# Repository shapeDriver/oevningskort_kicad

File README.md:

# oevningskort_kicad
Repeterar skolkunskap genom ett enkelt mönsterkortsprojekt som sammankopplar en Arduino Nano v3.x med enklare genomhålskomponenter.

Tungt baserad på HTM Workshops KiCad handledningsvideoserie: https://www.youtube.com/playlist?list=PLUOaI24LpvQPls1Ru_qECJrENwzD7XImd

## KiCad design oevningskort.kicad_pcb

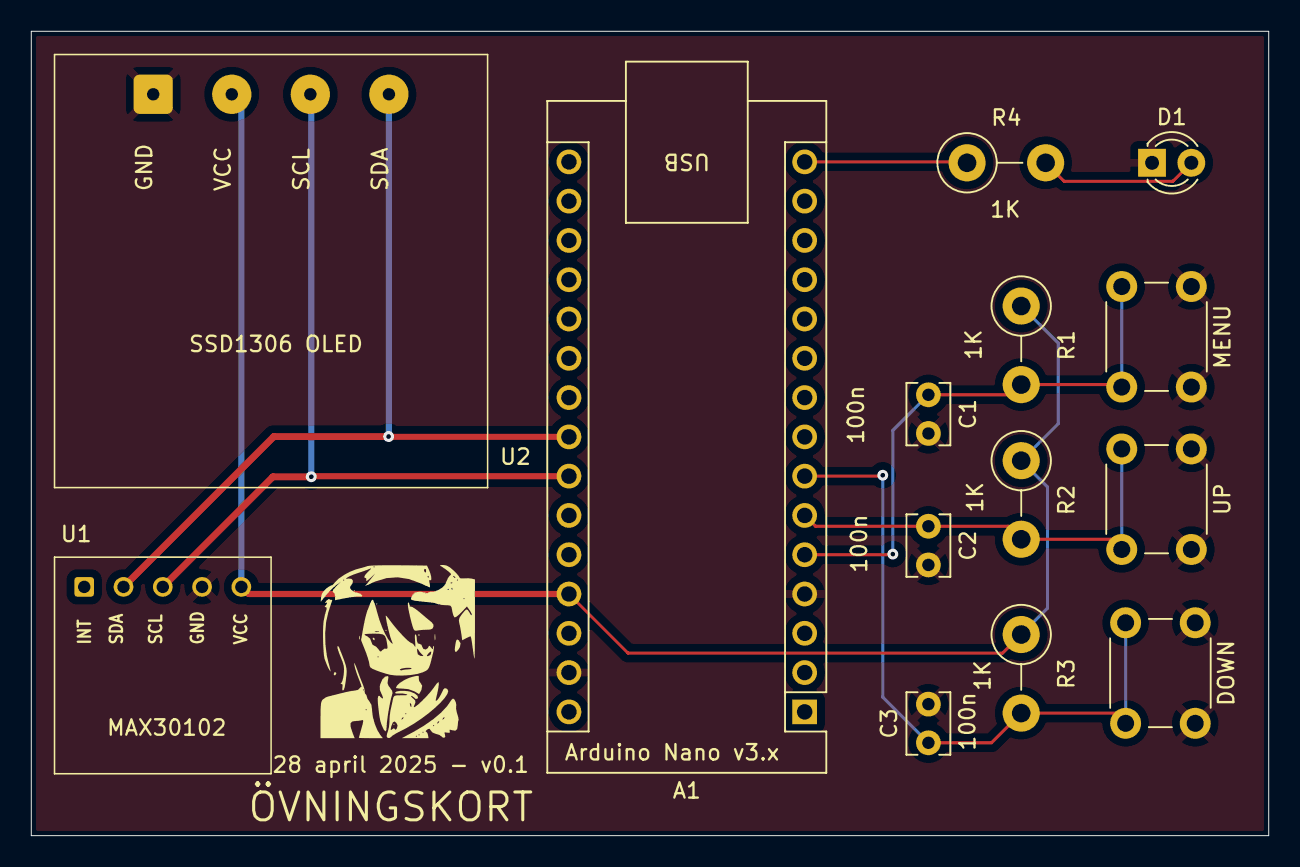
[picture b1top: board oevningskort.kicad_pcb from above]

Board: 2 copper layers, 80.0 x 52.0 mm, 14 parts (0 on the bottom side), 9 nets.

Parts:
A1: Arduino_Nano_v3.x; Arduino_Nano
C1, C2, C3: 100n; C_Disc_D3.8mm_W2.6mm_P2.50mm
D1: ALARM; LED_D3.0mm
DOWN: SW_Push; SW_PUSH_6mm
MENU: SW_Push; SW_PUSH_6mm
R1, R2, R3, R4: 1K; R_Axial_DIN0411_L9.9mm_D3.6mm_P5.08mm_Vertical
U1: MAX30102; MAX30102_module
U2: SSD1306
UP: SW_Push; SW_PUSH_6mm

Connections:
+5V: A1.27 (+5V), R1.1, R2.1, R3.1, U1.5 (VCC), U2.2 (VCC)
GND: A1.4 (GND), A1.29 (GND), C1.2, C2.2, C3.2, D1.1 (K), DOWN.1, MENU.1, U1.4 (GND), U2.1 (GND), UP.1
unnamed: A1.23 (A4), U1.2 (SDA), U2.4 (SDA)
unnamed: A1.24 (A5), U1.3 (SCL), U2.3 (SCL)
unnamed: A1.5 (D2), C1.1, MENU.2, R1.2
unnamed: A1.6 (D3), C2.1, R2.2, UP.2
unnamed: A1.7 (D4), C3.1, DOWN.2, R3.2
unnamed: A1.15 (D12), R4.1
unnamed: D1.2 (A), R4.2

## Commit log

2025-04-28 Add files via upload
    Project files for an exercise PCB with the intent to re-practice some KiCad skills.
2025-04-28 Delete build_a_kicad_project_schematic-backups directory
    Delete unneccesary backups.
2025-04-28 Delete oevningskort-backups directory
    Delete unneccesary backups.
2025-04-28 Add files via upload
    Added image from Aisler PCB builder preview.
2025-04-28 Update README.md
    Added a simple preview image of the PCB.
2025-04-28 Update README.md
    Grammatiska ändringar i beskrivningen.
2025-04-28 Update README.md
    Added credits where credits are due.
